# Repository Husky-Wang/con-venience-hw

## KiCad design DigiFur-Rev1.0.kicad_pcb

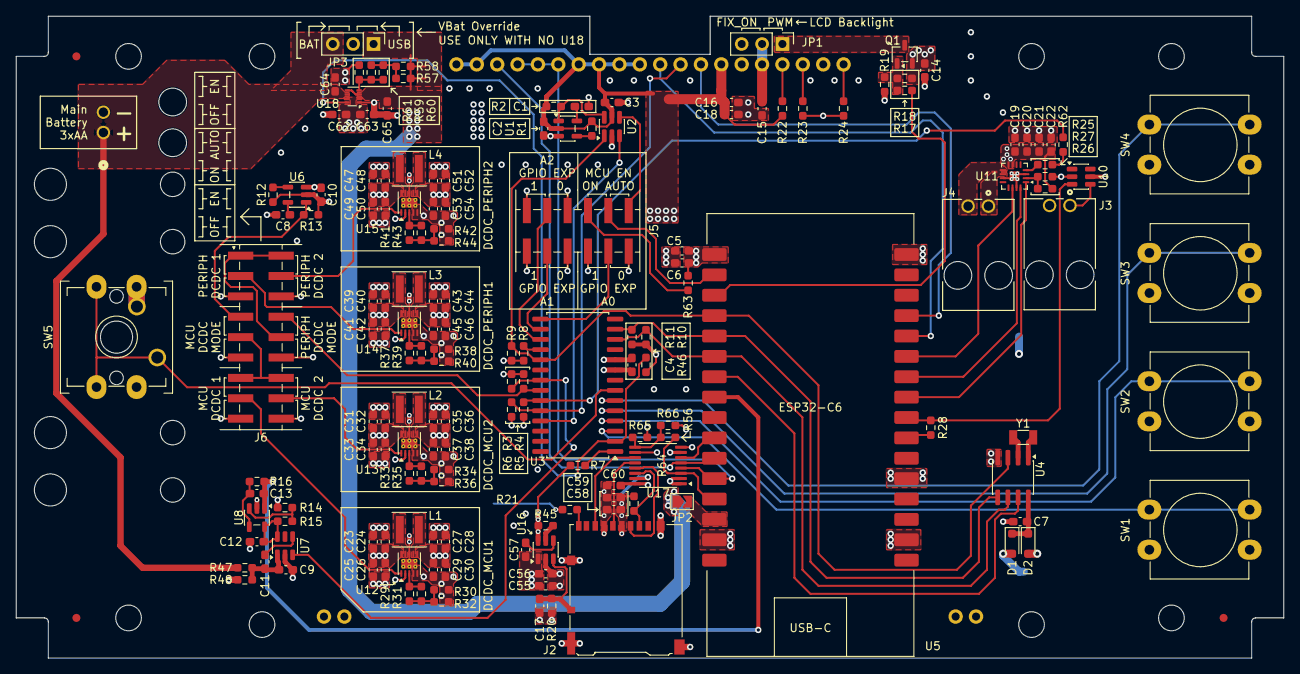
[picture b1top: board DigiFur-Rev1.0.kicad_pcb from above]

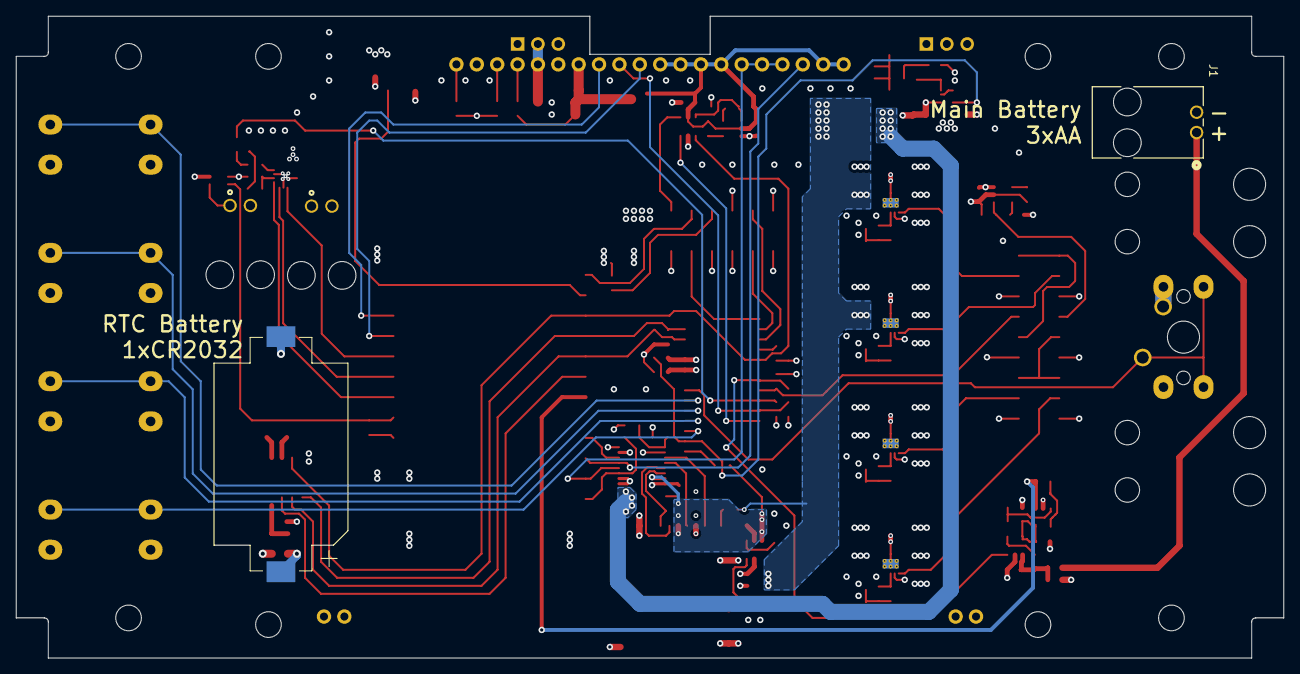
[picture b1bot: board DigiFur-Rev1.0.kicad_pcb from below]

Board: 4 copper layers, 158.0 x 80.0 mm, 172 parts (2 on the bottom side), 104 nets.

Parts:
BT1: A-BAT-CH-C8-EA-GSR3; BatteryHolder_Keystone_1060_1x2032
C1, C5, C6, C9, C14, C16, C18, C19, C20, C21, C22, C23, C24, C25, C26, C27, C28, C29, C30, C31, C32, C33, C34, C35, C36, C37, C38, C39, C40, C41, C42, C43, C44, C45, C46, C47, C48, C49, C50, C51, C52, C53, C54, C55, C56, C58, C59, C62, C63, C64, C65: 10u; C_0603_1608Metric_Pad1.08x0.95mm_HandSolder
C2, C3, C4, C7, C8, C10, C12, C15, C17, C60: 100n; C_0603_1608Metric_Pad1.08x0.95mm_HandSolder
C11: DNP; C_0603_1608Metric_Pad1.08x0.95mm_HandSolder
C13: 22p; C_0603_1608Metric_Pad1.08x0.95mm_HandSolder
C57: 470p; C_0603_1608Metric_Pad1.08x0.95mm_HandSolder
D1, D2: CUS520; D_SOD-323_HandSoldering
FID1, FID2, FID3: Fiducial; Fiducial_1mm_Mask3mm
H1, H2, H3, H4: MountingHole; MountingHole_3.2mm_M3
J1, J3, J4: 705510001; CONN_70551-xxxx_02_MOL
J2: Micro_SD_Card_Det_Hirose_DM3AT; microSD_HC_Hirose_DM3AT-SF-PEJM5
J5: Conn_02x06_Odd_Even; PinHeader_2x06_P2.54mm_Vertical_SMD
J6: Conn_02x09_Odd_Even; PinHeader_2x09_P2.54mm_Vertical_SMD
JP1, JP3: Jumper_3_Bridged12; PinHeader_1x03_P2.54mm_Vertical
JP2: SolderJumper_2_Open; SolderJumper-2_P1.3mm_Open_TrianglePad1.0x1.5mm
L1, L2, L3, L4: 2.2u; L_Coilcraft_XxL4020
Q1: SSM3J327R; SOT-23-3
R1, R2, R3, R4, R5, R6, R12, R13, R18, R19, R20, R46, R66: 1M; R_0603_1608Metric_Pad0.98x0.95mm_HandSolder
R7, R8, R10, R11: 1k; R_0603_1608Metric_Pad0.98x0.95mm_HandSolder
R9, R21, R25, R60, R62: 330k; R_0603_1608Metric_Pad0.98x0.95mm_HandSolder
R14, R15, R16, R61, R63: 10k; R_0603_1608Metric_Pad0.98x0.95mm_HandSolder
R17, R28: 330; R_0603_1608Metric_Pad0.98x0.95mm_HandSolder
R22, R23, R24: 1K; R_0603_1608Metric_Pad0.98x0.95mm_HandSolder
R26, R27, R47, R48, R56, R57, R65: 0; R_0603_1608Metric_Pad0.98x0.95mm_HandSolder
R29, R33, R37, R41, R64: 3.3k; R_0603_1608Metric_Pad0.98x0.95mm_HandSolder
R30, R34, R38, R42, R59: 33k; R_0603_1608Metric_Pad0.98x0.95mm_HandSolder
R31, R32, R35, R36, R39, R40, R43, R44, R45, R58: DNP; R_0603_1608Metric_Pad0.98x0.95mm_HandSolder
SW1, SW2, SW3, SW4, SW6: SW_Push; SW_PUSH-12mm_Wuerth-430476085716
SW5: MX2A-E1NW; SW_Cherry_MX_2.75u_PCB
U1, U6: TLV840MADL22DBVR; SOT-23-5
U2: NL17SZ10DBVT; SC-74-6_1.55x2.9mm_P0.95mm
U3: MCP23017x-x-SO; SOIC-28W_7.5x17.9mm_P1.27mm
U4: PCF85063AT; SOIC-8_3.9x4.9mm_P1.27mm
U5: ESP32-C6-DevKitC-1; ESP32-C6-DevKitC-Waveshare
U7, U16: TPS22917DBV; SOT-23-6
U8: OPA333 or TLV333 or TLV9041; SOT-23-5
U9: JLX256128G-931-PL_SPI; JLX256128G-931-PL
U10: USBLC6-2SC6; SOT-23-6
U11: MAX98357A; TQFN-16-1EP_3x3mm_P0.5mm_EP1.23x1.23mm
U12, U13, U14, U15: TPS63900; WSON-10-1EP_2.5x2.5mm_P0.5mm_EP1.2x2mm_ThermalVias
U17: SN74AXC4T774; TSSOP-16_4.4x5mm_P0.65mm
U18: TPS2117DRL; SOT-583-8
Y1: ECS-.327-12.5-34QCS-TR; Crystal_SMD_3215-2Pin_3.2x1.5mm

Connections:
+3.3V_MCU: C2.2, C3.1, C4.1, C5.2, C6.2, C16.1, C18.1, C27.1, C28.1, C29.1, C30.1, C35.1, C36.1, C37.1, C38.1, C60.2, D2.2 (A), J5.1, J5.2, J5.7, R1.1, R2.1, R8.1, R9.1, R10.1, R11.1, R22.2, R46.1, R63.1, R66.1, U1.2 (VDD), U2.5 (VCC), U3.9 (V_{DD}), U5.1 (3V3), U9.7 (VDD), U9.11 (VDD), U9.12 (VDD), U9.13 (VDD), U9.14 (VDD), U9.19 (VDD), U9.20 (VDD), U10.5 (VBUS), U12.6 (VOUT), U13.6 (VOUT), U17.1 (DIR1), U17.2 (DIR2), U17.7 (DIR3), U17.16 (VCCA)
+3.3V_PERIPH: C14.1, C19.1, C20.1, C21.1, C22.1, C43.1, C44.1, C45.1, C46.1, C51.1, C52.1, C53.1, C54.1, C55.1, C56.1, C57.1, JP1.3 (B), Q1.2 (S), R18.1, R21.2, R26.1, U11.7 (VDD), U11.8 (VDD), U14.6 (VOUT), U15.6 (VOUT), U16.1 (VIN)
+3.3V_SD: C58.1, C59.1, J2.4 (VDD), R7.1, R45.1, R64.1, U16.6 (VOUT), U17.15 (VCCB)
/Jumpers/PWR_MCU_EN_JP: J6.9, J6.13, J6.14
/Jumpers/PWR_PERIPH_EN_JP: J6.1, J6.2, J6.10
/MCU/I2C_SCL: R10.2, U3.12 (SCK), U4.6 (SCL), U5.6 (GPIO7)
/MCU/I2C_SDA: R11.2, U3.13 (SDA), U4.5 (SDA), U5.5 (GPIO6)
/MCU/MCU_SLEEP_REQ: U2.3, U3.25 (GPA4)
/MCU/MCU_SLOW_CLK: U4.7 (CLKOUT), U5.7 (GPIO0)
/MCU/~INT: R9.2, U2.1, U3.19 (INTB), U4.3 (~INT), U5.4 (GPIO5)
/Other Peripherals/SPI_CLK_ISOL: J2.5 (CLK), U17.12 (B3)
/Other Peripherals/SPI_MISO_ISOL: J2.7 (DAT0), U17.11 (B4)
/Other Peripherals/SPI_MOSI_ISOL: J2.3 (CMD), U17.13 (B2)
/Other Peripherals/SPI_~CS_SD_ISOL: J2.2 (DAT3/CD), R64.2, U17.14 (B1)
/Power Management/PR1: R59.2, R60.2, R61.1, U18.4 (PR1)
ACOM_OD: R28.2, U5.24 (GPIO19), U10.3 (I/O2)
ACOM_PU: R28.1, U5.23 (GPIO18)
BAT_MON_ADC: C13.1, R16.1, U5.8 (GPIO1), U8.1
BAT_MON_EN: R3.1, U3.21 (GPA0), U7.3 (ON)
DCDC_MCU1_EN: J6.15, U12.1 (EN)
DCDC_MCU2_EN: J6.16, U13.1 (EN)
DCDC_PERIPH1_EN: J6.3, U14.1 (EN)
DCDC_PERIPH2_EN: J6.4, U15.1 (EN)
GND: BT1.2 (-), C1.2, C2.1, C3.2, C4.2, C5.1, C6.1, C7.2, C8.2, C9.2, C10.1, C12.2, C14.2, C15.2, C16.2, C17.2, C18.2, C19.2, C20.2, C21.2, C22.2, C23.2, C24.2, C25.2, C26.2, C27.2, C28.2, C29.2, C30.2, C31.2, C32.2, C33.2, C34.2, C35.2, C36.2, C37.2, C38.2, C39.2, C40.2, C41.2, C42.2, C43.2, C44.2, C45.2, C46.2, C47.2, C48.2, C49.2, C50.2, C51.2, C52.2, C53.2, C54.2, C55.2, C56.2, C58.2, C59.2, C60.1, C62.2, C63.2, C64.2, C65.2, J1.2, J2.6 (VSS), J2.SH (SHIELD), J3.2, J5.5, J5.6, J5.11, J6.5, J6.6, J6.17, J6.18, R3.2, R4.2, R5.2, R6.2, R15.2, R19.2, R20.2, R23.2, R24.2, R27.2, R30.2, R32.2, R34.2, R36.2, R38.2, R40.2, R42.2, R44.2, R61.2, R65.2, SW1.2, SW2.2, SW3.2, SW4.2, SW5.2, SW6.2, U1.3 (GND), U2.2 (GND), U3.10 (V_{SS}), U4.4 (VSS), U5.15 (GND), U5.18 (GND), U5.21 (GND), U5.32 (GND), U6.3 (GND), U7.2 (GND), U8.2 (V-), U9.6 (VSS), U10.2 (GND), U11.3 (GND), U11.11 (GND), U11.15 (GND), U11.17 (PAD), U12.4 (CFG2), U12.5 (CFG3), U12.8 (GND), U12.11 (GND), U13.4 (CFG2), U13.5 (CFG3), U13.8 (GND), U13.11 (GND), U14.4 (CFG2), U14.5 (CFG3), U14.8 (GND), U14.11 (GND), U15.4 (CFG2), U15.5 (CFG3), U15.8 (GND), U15.11 (GND), U16.2 (GND), U17.8 (DIR4), U17.10 (GND), U18.1 (GND)
GPIO_EXP_A0: J5.9, U3.15 (A0)
GPIO_EXP_A1: J5.3, U3.16 (A1)
GPIO_EXP_A2: J5.4, U3.17 (A2)
I2S_BCLK: U5.26 (GPIO21), U11.16 (BCLK)
I2S_DATA: U5.25 (GPIO20), U11.1 (DIN)
I2S_LRCK: U5.27 (GPIO22), U11.14 (LRCLK)
LCD_D/~C: U5.29 (GPIO15), U9.8 (A0(RS))
LCD_LEDA: C15.1, JP1.2 (C), U9.5 (LEDA)
LCD_LEDA_PWM: R17.1, U5.3 (GPIO4)
LCD_~RST: R6.1, U3.24 (GPA3), U9.9 (~RST)
MCU_EN: J5.10, U5.2 (RST)
MCU_EN_JP: J5.12, U2.4
unnamed: BT1.1 (+), D1.2 (A)
unnamed: C7.1, D1.1 (K), D2.1 (K), U4.8 (VDD)
unnamed: J2.9 (DET_B), R21.1
unnamed: J3.1, U10.4 (I/O2)
unnamed: J4.1, U11.10 (OUTN)
unnamed: J4.2, U11.9 (OUTP)
unnamed: J5.8, R63.2
unnamed: JP1.1 (A), Q1.3 (D)
unnamed: JP2.2 (B), U5.14 (5V0)
unnamed: Q1.1 (G), R17.2, R18.2, R19.1
unnamed: R25.1, R62.2
unnamed: R29.2, R30.1, R31.2, R32.1
unnamed: R33.2, R34.1, R35.2, R36.1
unnamed: R37.2, R38.1, R39.2, R40.1
unnamed: R41.2, R42.1, R43.2, R44.1
unnamed: R57.2, R58.2, R59.1, R60.1
unnamed: C1.1, U1.5 (CT)
unnamed: R1.2, U1.4 (~MR)
unnamed: R2.2, U1.1 (~RESET), U2.6
unnamed: R7.2, U3.1 (GPB0)
unnamed: SW1.1, U3.3 (GPB2)
unnamed: SW2.1, U3.4 (GPB3)
unnamed: SW3.1, U3.5 (GPB4)
unnamed: SW4.1, U3.6 (GPB5)
unnamed: SW5.1, SW6.1, U3.7 (GPB6)
unnamed: R8.2, U3.18 (~RESET)
unnamed: U4.1 (OSCI), Y1.2
unnamed: U4.2 (OSCO), Y1.1
unnamed: C8.1, U6.5 (CT)
unnamed: R12.2, U6.4 (~MR)
unnamed: C11.2, U7.4 (CT)
unnamed: C9.1, C11.1, R47.2, R48.1, U7.1 (VIN)
unnamed: C12.1, R14.1, U7.6 (VOUT), U8.5 (V+)
unnamed: R14.2, R15.1, U8.3 (+)
unnamed: C13.2, R16.2, U8.4 (-)
unnamed: R24.1, U9.1 (ROM_IN)
unnamed: R23.1, U9.3 (ROM_SCK)
unnamed: R22.1, U9.4 (ROM_~CS)
unnamed: R26.2, R27.1, U11.2 (GAIN_SLOT)
unnamed: R25.2, U11.4 (~SD_MODE)
unnamed: R29.1, R31.1, U12.3 (CFG1)
unnamed: L1.1, U12.9 (LX1)
unnamed: L1.2, U12.7 (LX2)
unnamed: R33.1, R35.1, U13.3 (CFG1)
unnamed: L2.1, U13.9 (LX1)
unnamed: L2.2, U13.7 (LX2)
unnamed: R37.1, R39.1, U14.3 (CFG1)
unnamed: L3.1, U14.9 (LX1)
unnamed: L3.2, U14.7 (LX2)
unnamed: R41.1, R43.1, U15.3 (CFG1)
unnamed: L4.1, U15.9 (LX1)
unnamed: L4.2, U15.7 (LX2)
unnamed: C57.2, U16.4 (CT)
unnamed: R45.2, U16.5 (QOD)
unnamed: R56.2, R65.1, R66.2, U17.9 (~OE)
PWR_MCU_EN: J6.7, R13.2, U6.1 (~RESET)
PWR_PERIPH_EN: J6.8, R4.1, U3.22 (GPA1)
SD_DET: C17.1, J2.10 (DET_A), R20.1, U16.3 (ON)
SPI_CLK: U5.11 (GPIO11), U9.18 (SCK), U17.5 (A3)
SPI_MISO: U5.10 (GPIO10), U17.6 (A4)
SPI_MOSI: U5.12 (GPIO2), U9.15 (SDA), U9.16 (SDA), U9.17 (SDA), U17.4 (A2)
SPI_~CS_LCD: U5.28 (GPIO23), U9.10 (~CS)
SPI_~CS_SD: R56.1, U5.13 (GPIO3), U17.3 (A1)
SPK_EN: R5.1, R62.1, U3.23 (GPA2)
USB_PWR: R46.2, U3.2 (GPB1), U18.8 (ST)
VBAT: C10.2, C23.1, C24.1, C25.1, C26.1, C31.1, C32.1, C33.1, C34.1, C39.1, C40.1, C41.1, C42.1, C47.1, C48.1, C49.1, C50.1, C62.1, C63.1, J6.11, J6.12, JP3.2 (C), R12.1, R13.1, R48.2, U6.2 (VDD), U12.2 (SEL), U12.10 (VIN), U13.2 (SEL), U13.10 (VIN), U14.2 (SEL), U14.10 (VIN), U15.2 (SEL), U15.10 (VIN), U18.2 (VOUT), U18.7 (VOUT)
VBAT_CONN: C64.1, J1.1, JP3.3 (B), R47.1, U18.6 (VIN2)
VUSB: C65.1, JP2.1 (A), JP3.1 (A), R57.1, R58.1, U18.3 (VIN1), U18.5 (MODE)
